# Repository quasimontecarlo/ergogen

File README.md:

# Ergogen

***Ergonomic Keyboard Generator***

This is my fork of ergogen and includes the project files for quasikb, the source yaml can be found under src/quasikb.yaml, the resulting kicad files under /kb/ folder. This repo does also include external footprints from ceoloide.
https://github.com/ceoloide/ergogen-footprints

<br>

The project aims to provide a common configuration format to describe ***ergonomic*** 2D layouts and generate automatic plates, cases, as well as un-routed PCBs for them. The project grew out of (and is an integral part of) the [Absolem keyboard], and shares its [Discord] server as well.

<div align = center>
<br>
<br>
<br>

---

[![Button WebUI]][WebUI]
[![Button Documentation]][Documentation]
[![Button Discord]][Discord]
[![Button Donate]][Donate]

---

</div>

<br>
<br>

## Getting Started

Until there's a proper "Getting started" guide, try getting acquainted with **Ergogen** by following these steps in order:

<br>

1. Read the **[Documentation]**.
    
    D'uuh.
    They're not complete by any measure, but should give you a fairly good idea what you're dealing with here.

    <br>
    
2. Try one of the web-based deployments.

    [![Button Official]][WebUI]   
    [![Button Unofficial]][Unofficial]
   
    The unofficial deployment is probably better, tbh, and will soon be replacing the official one.
    Choose either one, then click things, look at outputs and see if things start to make sense.
   
    There is no need for you to download the **CLI** unless you want to do one of the following:
   
    - Preview in-development features
    - Use custom modifications
    - Contribute code
   
    <br>

3. Search the [`ergogen`][Topic] topic on GitHub.

    There, you can look at (and reverse engineer) a variety of real life configs using **Ergogen**.
    Pop them into the web UI to see what they do, tinker with them and things should start to make more sense.

    <br>

4. If a question persists after all of the above, feel free to ask it over on **[Discord]** and we'll do our best to help you out.

<br>

## Contributions

Feature ideas, documentation improvements, examples, tests, or pull requests welcome!
Get in touch on our **[Discord]**, and we can definitely find something you can help with, if you'd like to.

<br>

## Sponsors

Huge thanks go to everyone who chooses to support my work!
But even huger thanks are due to the following, *distinguished* sponsors:

- [perce](https://madebyperce.com/)
- [Cache](https://github.com/MvEerd)
- [Neil Gilmour](https://github.com/neilgilmour)
- [ochief](https://github.com/ochief)
- [Alyx Brett](https://github.com/alyx-brett)

<!----------------------------------------------------------------------------->

[Absolem keyboard]: https://zealot.hu/absolem
[Documentation]: https://docs.ergogen.xyz
[Discord]: http://discord.ergogen.xyz
[WebUI]: https://ergogen.xyz
[Unofficial]: https://ergogen.ceoloide.com/
[Topic]: https://github.com/topics/ergogen
[Donate]: https://github.com/sponsors/mrzealot

<!--------------------------------{ Buttons }---------------------------------->

[Button WebUI]: https://img.shields.io/badge/Deployment-37a779?style=for-the-badge&logoColor=white&logo=AppleArcade
[Button Unofficial]: https://img.shields.io/badge/Unofficial-yellow?style=for-the-badge
[Button Official]: https://img.shields.io/badge/Official-37a779?style=for-the-badge
[Button Documentation]: https://img.shields.io/badge/Documentation-1793D1?style=for-the-badge&logoColor=white&logo=GitBook
[Button Discord]: https://img.shields.io/badge/Discord-5865F2?style=for-the-badge&logoColor=white&logo=Discord
[Button Donate]: https://img.shields.io/badge/Donate-EA4AAA?style=for-the-badge&logoColor=white&logo=githubsponsors

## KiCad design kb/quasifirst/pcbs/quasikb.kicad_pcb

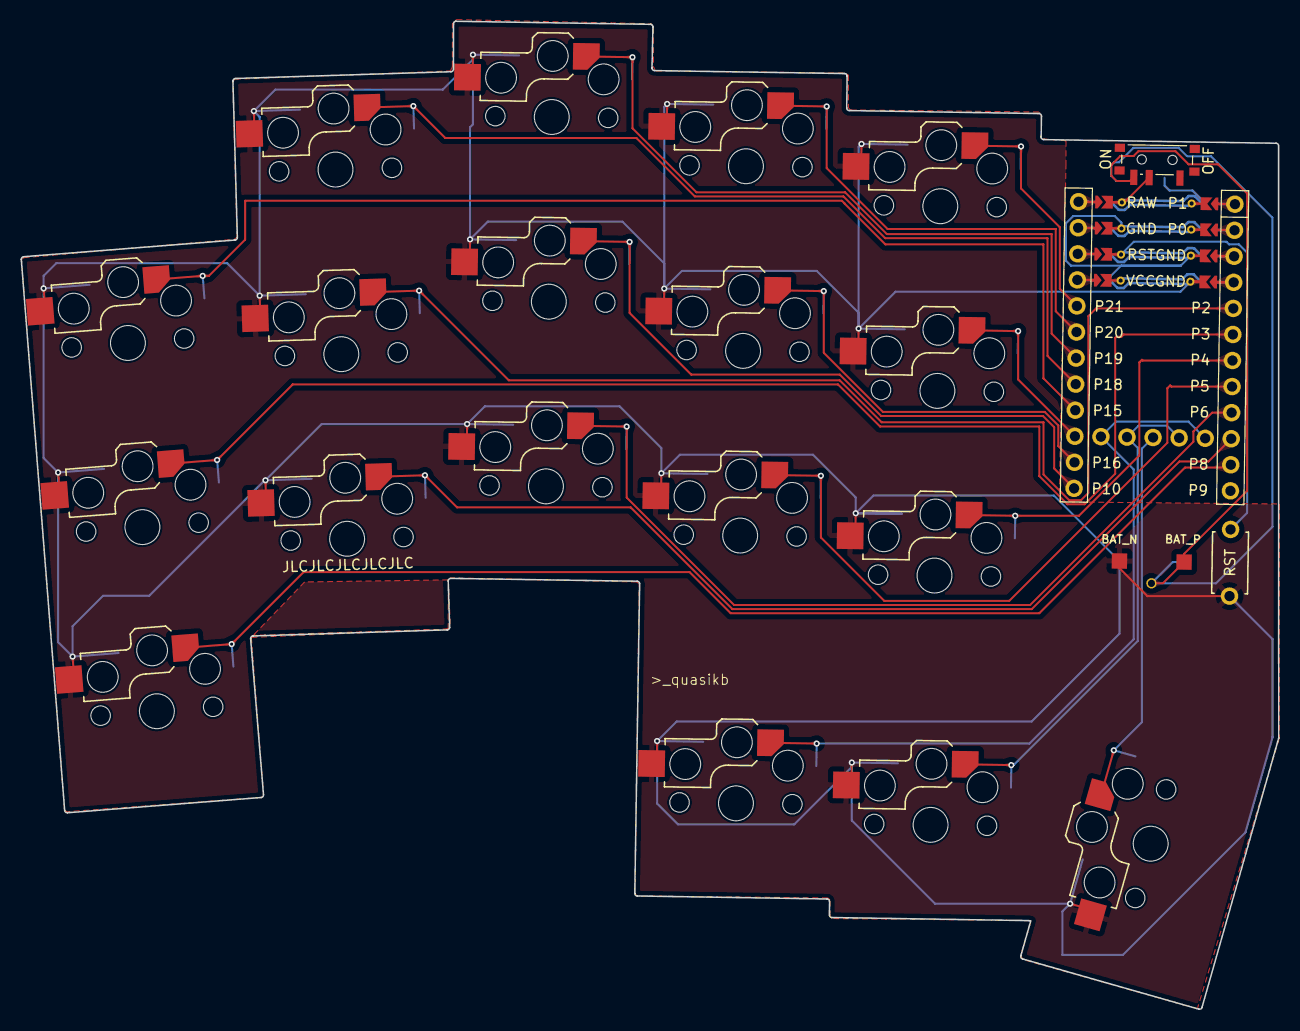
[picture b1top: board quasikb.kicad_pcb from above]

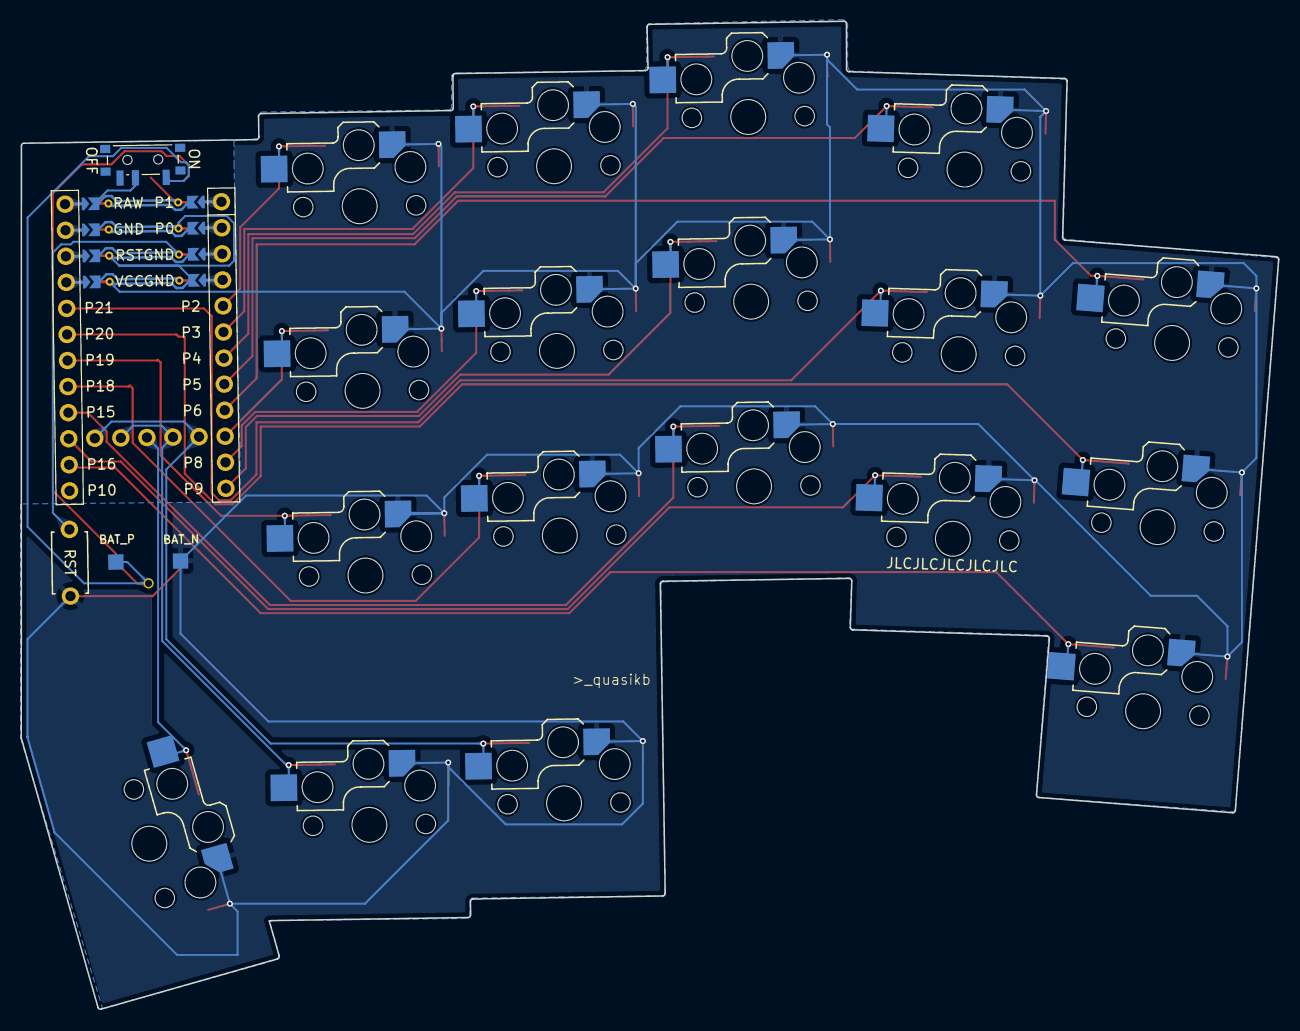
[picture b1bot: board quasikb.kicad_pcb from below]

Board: 2 copper layers, 122.5 x 96.3 mm, 23 parts (18 on the bottom side), 22 nets.

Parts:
MCU1: mcu_nice_nano
PAD1, PAD2: SMDPad
PWR1: power_switch_smd_side
RST1: reset_switch_tht_top
S1, S2, S3, S4, S5, S6, S7, S8, S9, S10, S11, S12, S13, S14, S15, S16, S17, S18: switch_choc_v1_v2

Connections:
BAT_P: PAD2.1, PWR1.1, PWR1.3
GND: MCU1.103, MCU1.104, MCU1.123, PAD1.1, RST1.2, S1.1, S1.2, S2.1, S2.2, S3.1, S3.2, S4.1, S4.2, S5.1, S5.2, S6.1, S6.2, S7.1, S7.2, S8.1, S8.2, S9.1, S9.2, S10.1, S10.2, S11.1, S11.2, S12.1, S12.2, S13.1, S13.2, S14.1, S14.2, S15.1, S15.2, S16.1, S16.2, S17.1, S17.2, S18.1, S18.2
RAW: MCU1.124, PWR1.2
RST: MCU1.122, RST1.1
matrix_index_bottom: MCU1.8, S10.1, S10.2
matrix_index_home: MCU1.14, S11.1, S11.2
matrix_index_top: MCU1.19, S12.1, S12.2
matrix_inner_bottom: MCU1.7, S13.1, S13.2
matrix_inner_home: MCU1.15, S14.1, S14.2
matrix_inner_top: MCU1.20, S15.1, S15.2
matrix_middle_bottom: MCU1.9, S7.1, S7.2
matrix_middle_home: MCU1.13, S8.1, S8.2
matrix_middle_top: MCU1.18, S9.1, S9.2
matrix_pinky_bottom: MCU1.11, S1.1, S1.2
matrix_pinky_home: MCU1.6, S2.1, S2.2
matrix_pinky_top: MCU1.16, S3.1, S3.2
matrix_ring_bottom: MCU1.10, S4.1, S4.2
matrix_ring_home: MCU1.5, S5.1, S5.2
matrix_ring_top: MCU1.17, S6.1, S6.2
thumb_innit: MCU1.25, MCU1.28, S16.1, S16.2
thumb_middle: MCU1.26, MCU1.29, S17.1, S17.2
thumb_reachy: MCU1.27, S18.1, S18.2

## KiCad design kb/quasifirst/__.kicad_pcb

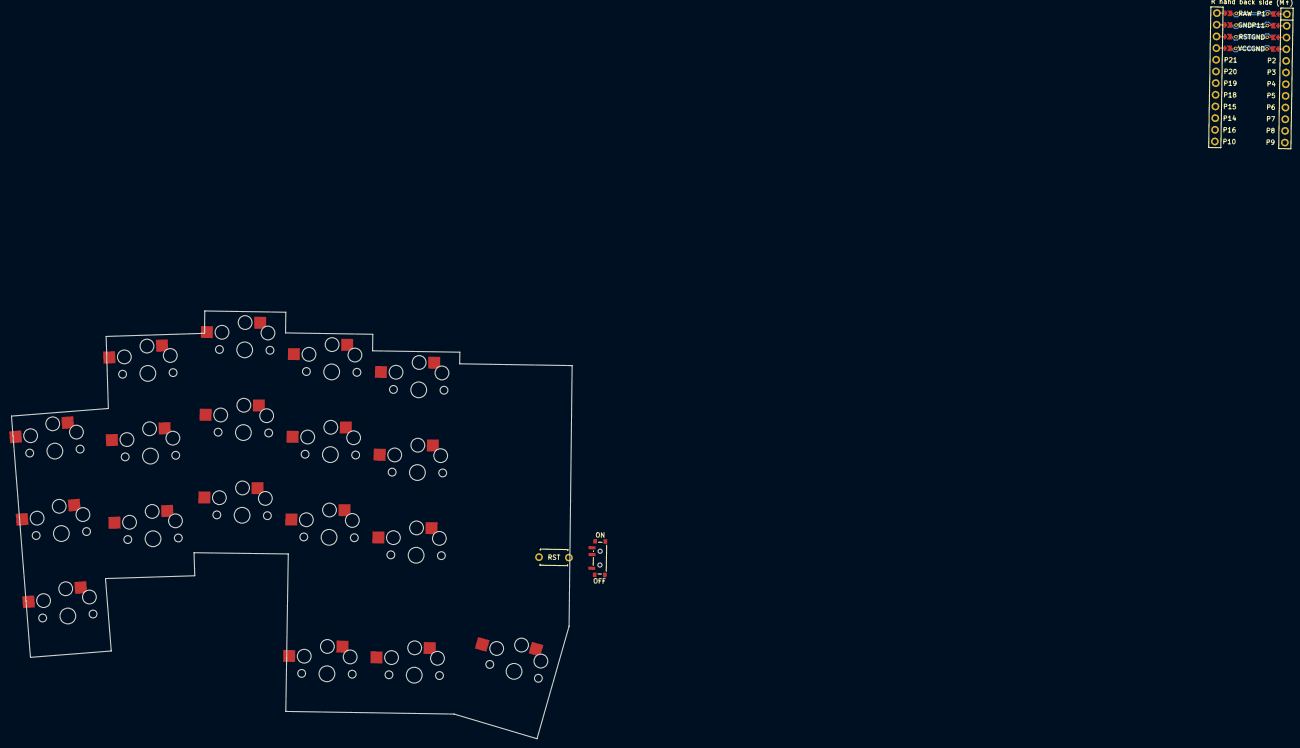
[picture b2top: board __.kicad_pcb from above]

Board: 2 copper layers, 122.0 x 93.1 mm, 21 parts (0 on the bottom side), 22 nets.

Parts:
MCU1: mcu_nice_nano
PWR1: power_switch_smd_side
RST1: reset_switch_tht_top
S1, S2, S3, S4, S5, S6, S7, S8, S9, S10, S11, S12, S13, S14, S15, S16, S17, S18: PG1350

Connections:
BAT_P: PWR1.1, PWR1.3
GND: MCU1.103, MCU1.104, MCU1.123, RST1.2, S1.2, S2.2, S3.2, S4.2, S5.2, S6.2, S7.2, S8.2, S9.2, S10.2, S11.2, S12.2, S13.2, S14.2, S15.2, S16.2, S17.2, S18.2
RAW: MCU1.124, PWR1.2
RST: MCU1.122, RST1.1
matrix_index_bottom: MCU1.8, S10.1
matrix_index_home: MCU1.13, S11.1
matrix_index_top: MCU1.19, S12.1
matrix_inner_bottom: MCU1.9, S13.1
matrix_inner_home: MCU1.101, S14.1
matrix_inner_top: MCU1.20, S15.1
matrix_middle_bottom: MCU1.7, S7.1
matrix_middle_home: MCU1.14, S8.1
matrix_middle_top: MCU1.18, S9.1
matrix_pinky_bottom: MCU1.5, S1.1
matrix_pinky_home: MCU1.16, S2.1
matrix_pinky_top: MCU1.10, S3.1
matrix_ring_bottom: MCU1.6, S4.1
matrix_ring_home: MCU1.15, S5.1
matrix_ring_top: MCU1.17, S6.1
thumb_innit: MCU1.102, S16.1
thumb_middle: MCU1.11, S17.1
thumb_reachy: MCU1.12, S18.1

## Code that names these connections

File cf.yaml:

meta:
  engine: 4.1.0
  author: quasimontecarlo
units:
  center_shift_x: 170
  center_shift_y: -165

points:
  zones:
    matrix:
      anchor:
        shift: [ center_shift_x, center_shift_y]
      columns:
        pinky:
          key.splay: 0.25cx
          rows:
            home:
              column_net: 2
        ring:
          key.stagger: 0.85cx
          key.spread: 1.1cx
          key.splay: -0.15cx
        middle:
          key.stagger: 0.25cx
          key.splay: -0.15cx
          key.spread: 1.085cx
        index:
          key.stagger: -0.25cx
        inner:
          key.stagger: -0.2cx
      rows:
        bottom.padding: cx
        home.padding: cx
        top.padding: cx
    thumb:
      anchor:
        ref: matrix_index_bottom
        shift: [0.0, -1.65cx]
      columns:
        innit:
          key.name: thumb_innit
        middle:
          key.name: thumb_middle
        reachy:
          key.spread: cx
          key.splay: -15
          key.origin: [0.35cx, -0.75cx]
          key.name: thumb_reachy

outlines:
  raw:
    - what: rectangle
      where: true
      size: [cx, cy]
  board:  
    - what: polygon
      points:
        - ref: thumb_reachy
          shift: [0.49cx, 0.749cy]
        - ref: thumb_reachy
          shift: [0.49cx, -0.749cy]
        - ref: thumb_middle
          shift: [0.49cx, -0.49cy]
        - ref: thumb_innit
          shift: [0.49cx, -0.49cy]
        - ref: thumb_innit
          shift: [-0.49cx, -0.49cy]
        - ref: matrix_index_bottom
          shift: [-0.49cx, -0.221cy]
        - ref: matrix_ring_bottom
          shift: [+0.49cx, -0.195cy]
        - ref: matrix_ring_bottom
          shift: [+0.49cx, -0.49cy]
        - ref: matrix_ring_bottom
          shift: [-0.59cx, -0.49cy]
        - ref: matrix_pinky_bottom
          shift: [+0.49cx, -0.49cy]
        - ref: matrix_pinky_bottom
          shift: [-0.49cx, -0.49cy]
        - ref: matrix_pinky_top
          shift: [-0.49cx, 0.49cy]
        - ref: matrix_pinky_top
          shift: [0.685cx, 0.49cy]
        - ref: matrix_ring_top
          shift: [-0.49cx, 0.49cy]
        - ref: matrix_ring_top
          shift: [0.7cx, 0.49cy]
        - ref: matrix_middle_top
          shift: [-0.49cx, 0.49cy]
        - ref: matrix_middle_top
          shift: [0.49cx, 0.49cy]
        - ref: matrix_index_top
          shift: [-0.565cx, 0.49cy]
        - ref: matrix_index_top
          shift: [0.49cx, 0.49cy]
        - ref: matrix_index_top
          shift: [0.49cx, 0.49cy]
        - ref: matrix_inner_top
          shift: [-0.565cx, 0.49cy]
        - ref: matrix_inner_top
          shift: [0.49cx, 0.49cy]
        - ref: matrix_inner_home
          shift: [0.49cx, 1.4cy]
        - ref: matrix_inner_home
          shift: [1.85cx, 1.4cy]
      fillet: 0

  keycaps:
    - what: rectangle
      where: true
      size: [1cx - 0.5, 1cy - 0.5] # Choc keycaps are 17.5 x 16.5
      operation: stack
  keycaps15:
    - what: rectangle
      where: thumb_reachy
      size: [1cx - 0.5, 1.5cy - 0.5] # 1.5 choc cap
      operation: stack
  plate:
    - board
    - -keycaps
    - -keycaps15

pcbs:
  quasikeyboard:
    template: kicad8
    outlines:
      board:
        outline: board
      keycaps:
        outline: keycaps
        layer: Eco1.User
    footprints:
      choc_hotswap:
        what: choc
        where: true
        params:
          from: "{{name}}"
          to: GND
          keycaps: true
          reverse: true
          hotswap: true
      mcu:
        what: mcu_nice_nano
        where:
          - ref: matrix_inner_home
            shift: [10cx, 5cx]
        params:
          reversible: true
          only_required_jumpers: true
          P7: matrix_pinky_top
          P7_label: P7
          P18: matrix_ring_top
          P18_label: P18
          P19: matrix_middle_top
          P19_label: P19
          P20: matrix_index_top
          P20_label: P20
          P21: matrix_inner_top
          P21_label: P21
          P15: matrix_pinky_home
          P15_label: P15
          P14: matrix_ring_home
          P14_label: P14
          P16: matrix_middle_home
          P16_label: P16
          P10: matrix_index_home
          P10_label: P10
          P1: matrix_inner_home
          P1_label: P1
          P2: matrix_pinky_bottom
          P2_label: P2
          P3: matrix_ring_bottom
          P3_label: P3
          P4: matrix_middle_bottom
          P4_label: P4
          P5: matrix_index_bottom
          P5_label: P5
          P6: matrix_inner_bottom
          P6_label: P6
          P0: thumb_innit
          P0_label: P11
          P8: thumb_middle
          P8_label: P8
          P9: thumb_reachy
          P9_label: P9

      reset:
        what: ceoloide/reset_switch_tht_top
        where:
          ref: matrix_inner_bottom
          shift: [30, 0]
        params:
          reversible: true
          from: GND
          to: RST
      power:
        what: ceoloide/power_switch_smd_side
        where:
          ref: matrix_inner_bottom
          shift: [40, 0]
        params:
          reversible: true
          from: BAT_P
          to: RAW
      bat:
        what: bat
        where:
          ref: matrix_inner_bottom
          shift: [40, -15]
          rotate: 180
        params:
          neg: GND

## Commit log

2025-02-03 adding custom footprints and my own config yaml
2025-02-03 removing submodule and adding files
2025-02-03 changing places
2025-02-03 first build
2025-02-04 adding components and refining placements and connections
2025-02-05 swapped chocs for ceoloide ones, reworked nets a bit, started to improve board layout, flipped thumb switch
2025-02-06 desing phase should be over, might have to come back with tweaks now that will start trace routing
2025-02-07 stuck on figuring out the right pins
2025-02-07 updated the mcu with the extra pins to get thumbs working, worked on the nets and mcu connections
2025-02-08 worked on switches, mcu and little improvements
2025-02-08 first traces test
2025-02-09 finished routing, checked for issues, added eyesdropping
2025-02-10 adding ground area
2025-02-10 refreshing the gerber.zip
2025-02-10 upading with new gerber.zip
2025-02-10 updating the kb signature
2025-02-10 just saving the files
2025-03-05 latest update to quasikb code and kicad file, updated readme
